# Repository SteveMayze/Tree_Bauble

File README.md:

# Tree_Bauble

## Basic Design
The Tree Bauble is simply a Christmas tree ornament that will contain some blinking LEDs. 
The concept of the design is to take a clear plastic ornament and build into this a main 
board with six arcs of flexible boards that would contain the LEDs.

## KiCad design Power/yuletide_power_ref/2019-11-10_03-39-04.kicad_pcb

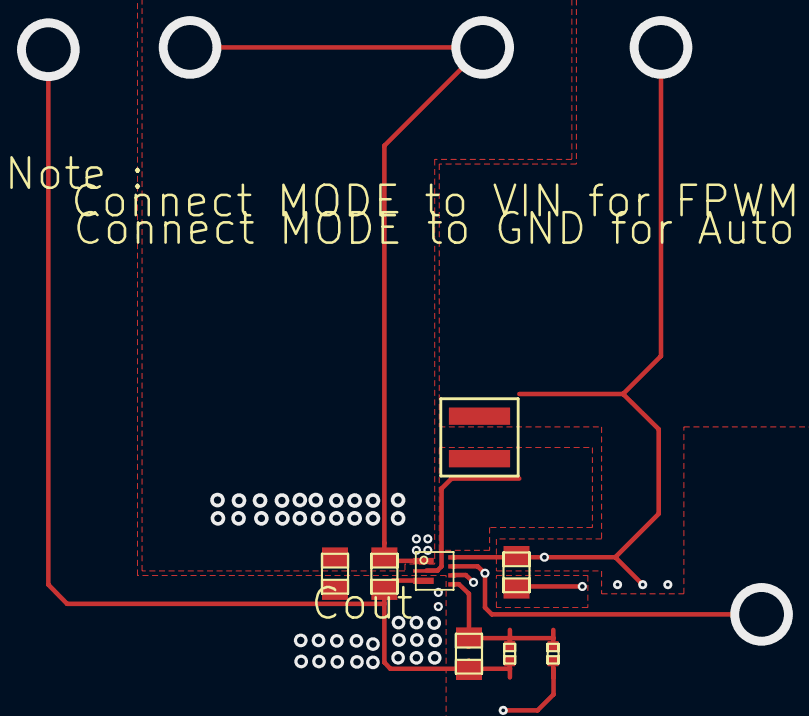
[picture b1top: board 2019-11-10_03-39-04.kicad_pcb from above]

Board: 10 copper layers, 13 parts (0 on the bottom side), 6 nets.

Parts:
Cff: 0805
Cin: 0805
Cout_1, Cout_2: 0805
GND, GND1: TP-1502
L1: XFL4020
MODE: TP-1502
Rfbb: 0402
Rfbt: 0402
U1: RWU0007A
VIN: TP-1502
VOUT: TP-1502

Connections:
0: Cin.2, Cout_1.2, Cout_2.2, GND.1, GND1.1, Rfbb.2, U1.1
2: Cin.1, L1.1, U1.5, U1.7, VIN.1
3: Cff.2, Rfbb.1, Rfbt.2, U1.4
5: Cff.1, Cout_1.1, Cout_2.1, Rfbt.1, U1.3, VOUT.1
8: MODE.1, U1.6
12: L1.2, U1.2

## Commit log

2019-11-10 README.md added
2019-11-10 Initial Checkin
